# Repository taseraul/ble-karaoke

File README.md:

# ble-karaoke
Audio mixer with balanced microphone and bluetooth input, great for karaoke parties

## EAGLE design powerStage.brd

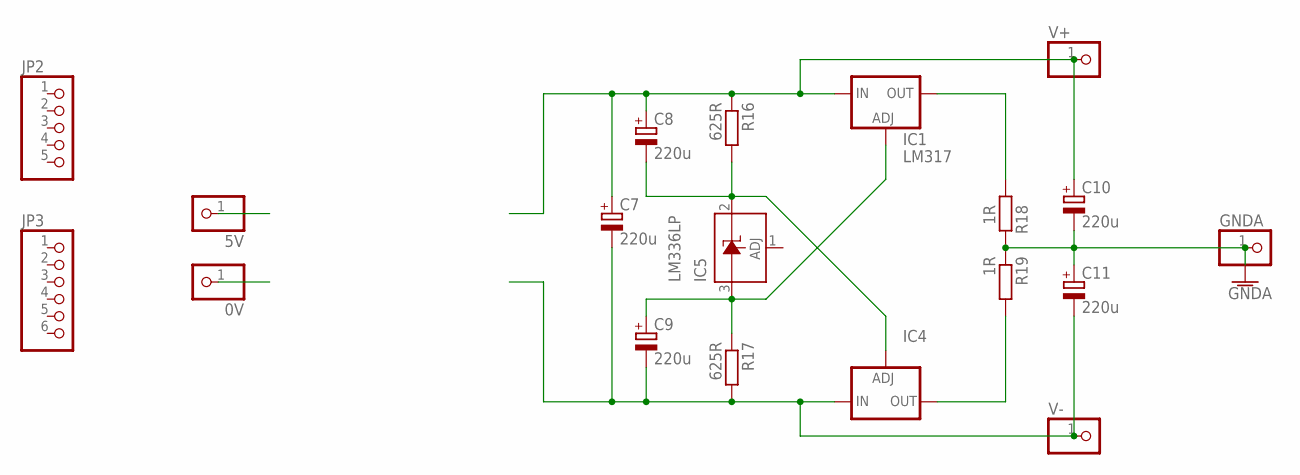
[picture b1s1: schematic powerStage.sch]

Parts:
0V, 5V: PINHD-1X1; 1X01
C7, C8, C9, C10, C11: 220u; E2-5
GNDA: PINHD-1X1; 1X01
IC1: LM317; TO220L1
IC4: LM337TL; 337TL
IC5: LM336LP; TO92
JP2: PINHD-1X5; 1X05
JP3: PINHD-1X6; 1X06
R16, R17: 625R; 0207/7
R18, R19: 1R; 0207/7
V+: PINHD-1X1; 1X01
V-: PINHD-1X1; 1X01

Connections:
GNDA: C10.-, C11.+, GNDA.1, R18.2, R19.1
unnamed: C7.+, C8.+, C10.+, IC1.3 (IN), R16.1, V+.1
unnamed: C7.-, C9.-, C11.-, IC4.2 (IN), R17.2, V-.1
unnamed: C9.+, IC1.1 (ADJ), IC5.3 (A), R17.1
unnamed: C8.-, IC4.1 (ADJ), IC5.2 (C), R16.2
unnamed: IC1.2 (OUT), R18.1
unnamed: IC4.3 (OUT), R19.2

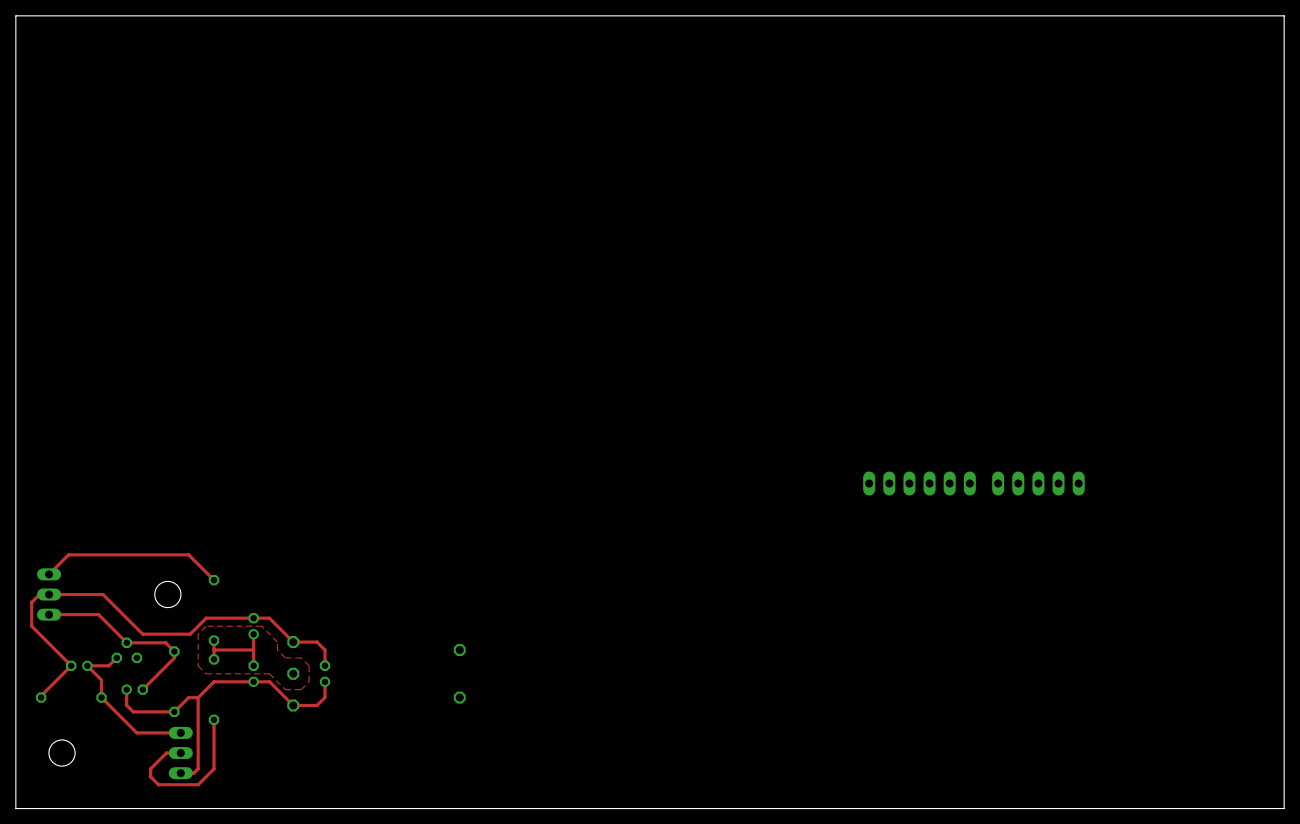
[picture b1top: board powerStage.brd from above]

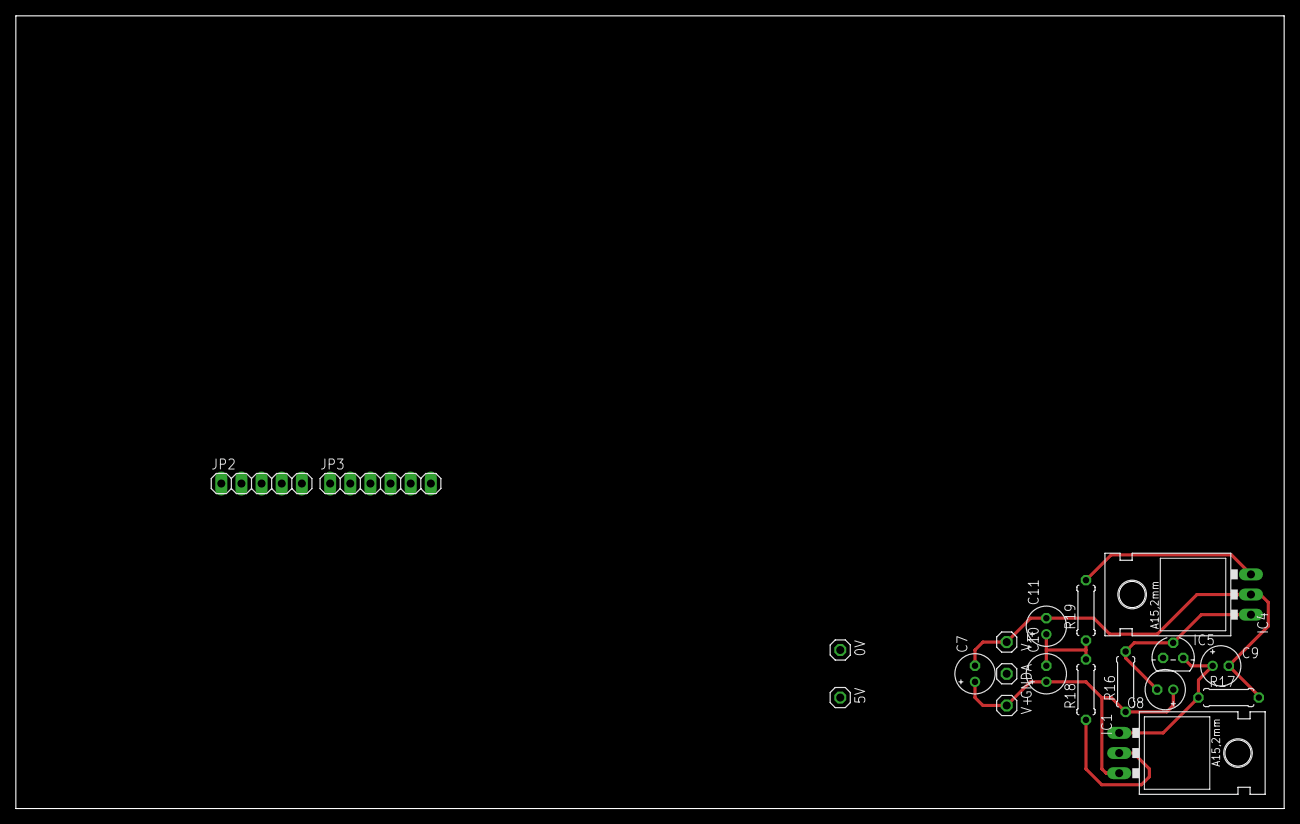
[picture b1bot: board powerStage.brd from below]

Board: 2 copper layers, 160.0 x 100.0 mm, 19 parts (19 on the bottom side), 7 nets.

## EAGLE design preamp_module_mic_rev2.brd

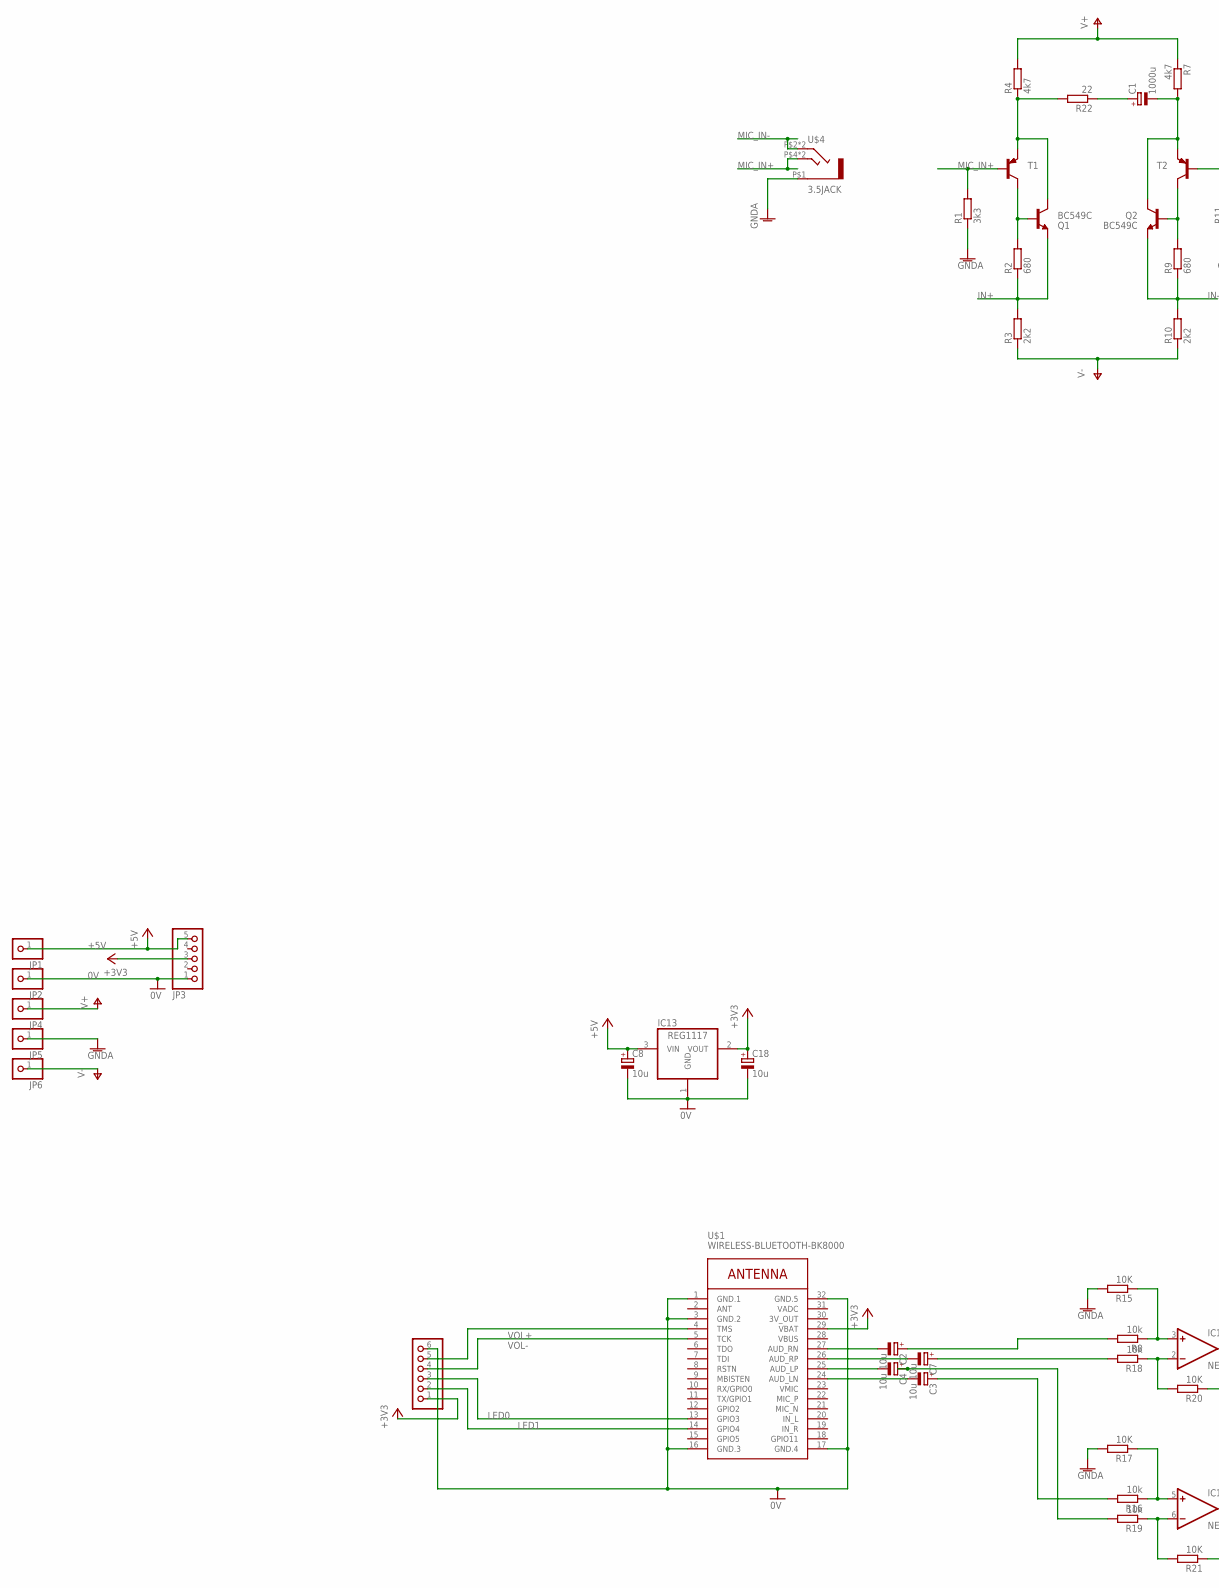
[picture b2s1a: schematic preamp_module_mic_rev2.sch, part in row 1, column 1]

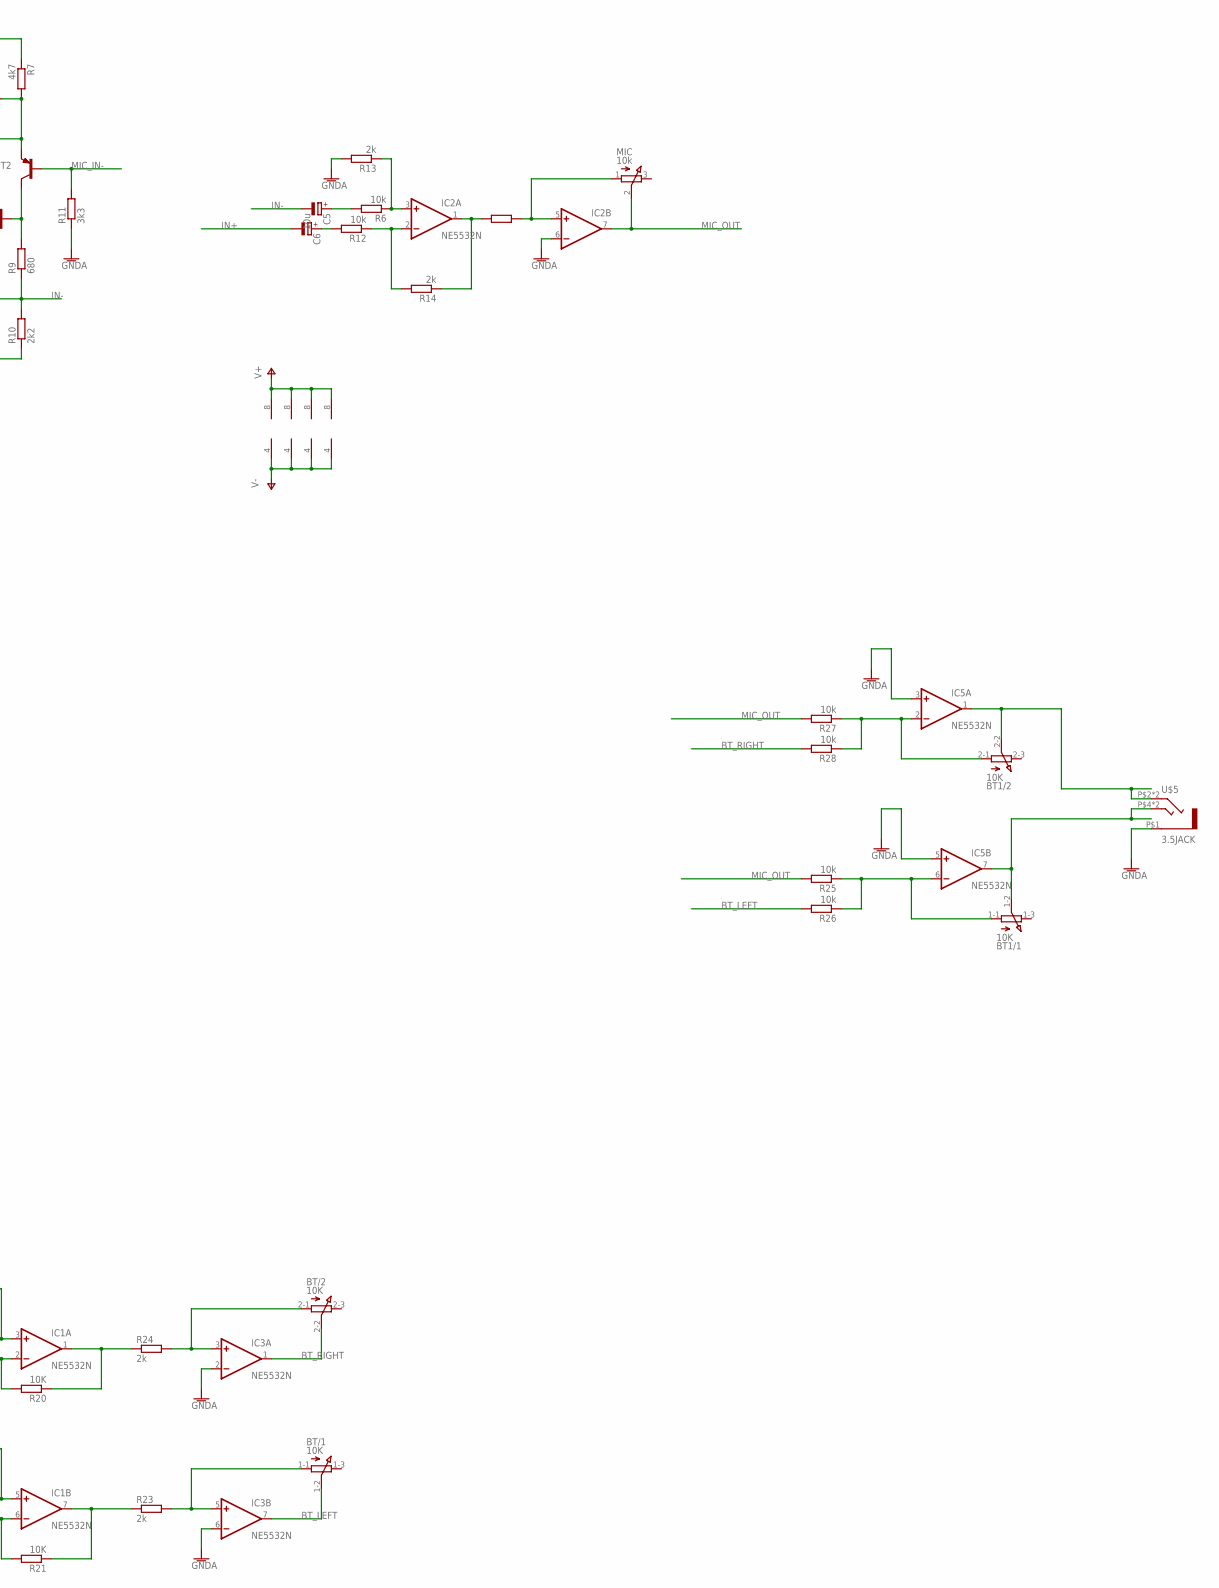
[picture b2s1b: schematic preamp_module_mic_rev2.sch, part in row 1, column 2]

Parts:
BT, BT1: 10K; 3RP/1610G
C1: 1000u; E5-5
C2, C3, C4, C5, C6, C7, C8, C18: 10u; E2-5
IC1, IC2, IC3, IC5: NE5532N; DIL08
IC13: REG1117; SOT223
JP1, JP2, JP4, JP5, JP6: PINHD-1X1; 1X01
JP3: PINHD-1X5; 1X05
JP7: PINHD-1X6; 1X06
MIC: 10k; 3RP/1610N
Q1, Q2: BC549C; TO92-EBC
R1, R11: 3k3; 0207/10
R2, R9: 680; 0207/10
R3, R10: 2k2; 0207/10
R4, R7: 4k7; 0207/10
R5, R13, R14, R23, R24: 2k; 0207/10
R6, R8, R12, R16, R18, R19, R25, R26, R27, R28: 10k; 0207/10
R15, R17, R20, R21: 10K; 0207/10
R22: 22; 0207/10
T1, T2: 2N4403-PNP-TO92-EBC; TO92-EBC
U$1: WIRELESS-BLUETOOTH-BK8000
U$4, U$5: 3.5JACK

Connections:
0V: C8.-, C18.-, IC13.1 (GND), JP2.1, JP3.1, JP7.6, U$1.1 (GND.1), U$1.3 (GND.2), U$1.16 (GND.3), U$1.17 (GND.4), U$1.32 (GND.5)
3V_OUT: U$1.30 (3V_OUT)
+3V3: C18.+, IC13.2 (VOUT), JP3.3, JP7.1, U$1.29 (VBAT)
+5V: C8.+, IC13.3 (VIN), JP1.1, JP3.5
BT_LEFT: BT.1-2 (S), IC3.7 (OUT), R26.2
BT_RIGHT: BT.2-2 (S), IC3.1 (OUT), R28.2
GNDA: IC2.6 (-IN), IC3.2 (-IN), IC3.6 (-IN), IC5.3 (+IN), IC5.5 (+IN), JP5.1, R1.1, R11.1, R13.2, R15.2, R17.2, U$4.P$1 (1), U$5.P$1 (1)
IN+: C6.-, Q1.E, R2.1, R3.2
IN-: C5.-, Q2.E, R9.1, R10.2
LED0: JP7.3, U$1.13 (GPIO3)
LED1: JP7.2, U$1.14 (GPIO4)
MIC_IN+: R1.2, T1.B, U$4.P$4 (3), U$4.P$5 (3)
MIC_IN-: R11.2, T2.B, U$4.P$2 (2), U$4.P$3 (2)
MIC_OUT: IC2.7 (OUT), MIC.2 (S), R25.2, R27.2
unnamed: Q1.B, R2.2, T1.C
unnamed: Q2.B, R9.2, T2.C
unnamed: IC2.5 (+IN), MIC.1 (A), R5.2
unnamed: C1.-, Q2.C, R7.2, T2.E
unnamed: C2.-, U$1.27 (AUD_RN)
unnamed: Q1.C, R4.1, R22.2, T1.E
unnamed: IC1.3 (+IN), R8.1, R15.1
unnamed: IC1.5 (+IN), R16.1, R17.1
unnamed: C2.+, R8.2
unnamed: C1.+, R22.1
unnamed: C6.+, R12.2
unnamed: IC2.2 (-IN), R12.1, R14.2
unnamed: C5.+, R6.2
unnamed: IC2.3 (+IN), R6.1, R13.1
unnamed: IC2.1 (OUT), R5.1, R14.1
unnamed: C3.-, U$1.24 (AUD_LN)
unnamed: C3.+, R16.2
unnamed: IC1.2 (-IN), R18.1, R20.2
unnamed: IC1.6 (-IN), R19.1, R21.2
unnamed: C7.+, R18.2
unnamed: IC1.1 (OUT), R20.1, R24.1
unnamed: IC1.7 (OUT), R21.1, R23.1
unnamed: BT.1-1 (A), IC3.5 (+IN), R23.2
unnamed: BT.2-1 (A), IC3.3 (+IN), R24.2
unnamed: BT1.2-1 (A), IC5.2 (-IN), R27.1, R28.1
unnamed: BT1.1-1 (A), IC5.6 (-IN), R25.1, R26.1
unnamed: BT1.2-2 (S), IC5.1 (OUT), U$5.P$2 (2), U$5.P$3 (2)
unnamed: BT1.1-2 (S), IC5.7 (OUT), U$5.P$4 (3), U$5.P$5 (3)
unnamed: C4.-, U$1.25 (AUD_LP)
unnamed: C7.-, U$1.26 (AUD_RP)
unnamed: C4.+, R19.2
V+: IC1.8 (V+), IC2.8 (V+), IC3.8 (V+), IC5.8 (V+), JP4.1, R4.2, R7.1
V-: IC1.4 (V-), IC2.4 (V-), IC3.4 (V-), IC5.4 (V-), JP6.1, R3.1, R10.1
VADC: U$1.31 (VADC)
VOL+: JP7.5, U$1.4 (TMS)
VOL-: JP7.4, U$1.5 (TCK)

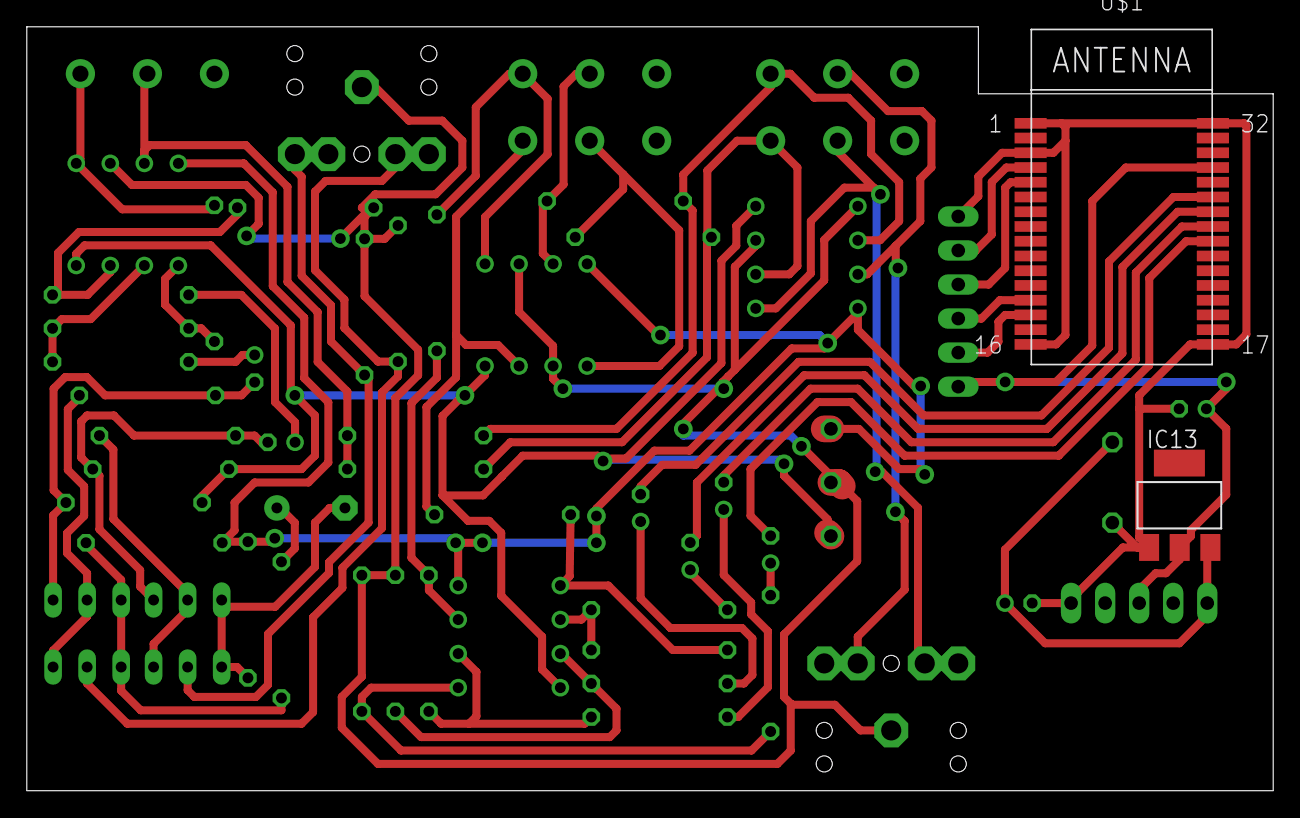
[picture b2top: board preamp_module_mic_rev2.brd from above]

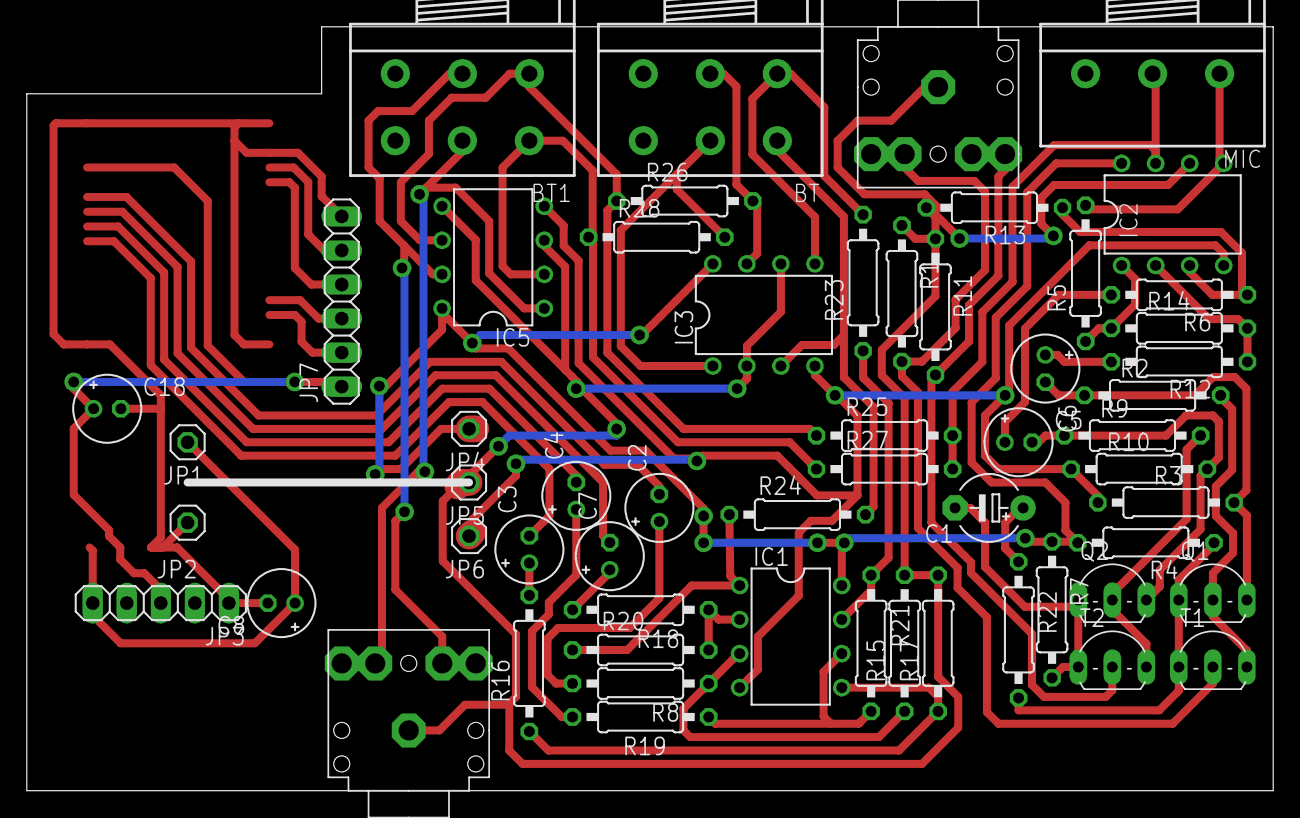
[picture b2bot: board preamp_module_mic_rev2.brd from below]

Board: 2 copper layers, 93.0 x 57.0 mm, 59 parts (57 on the bottom side), 48 nets.

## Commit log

2020-07-01 Fixed input volume control
2020-07-01 power management WIP

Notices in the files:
parts and their libraries:
diy-modules: Released under the Creative Commons Attribution 4.0 International License: http://creativecommons.org/licenses/by/4.0
